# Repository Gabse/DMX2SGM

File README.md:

DMX2SGM
=
DMX512 to Dual SGM256 Converter

=
This simple device converts a standard DMX512 Signal into two SGM256 signals.

It lets you reuse your old SGM gear with almost any standard DMX controller on the market.

The device has 2 independent outputs for DMX channel 1 to 256 and 257 to 512 and can be powered by ether one of them.

Due to its small form factor it can be installed nearly anywhere in the SGM signal path replacing old SGM Regia lighting desks directly. 

9 Dip Swithes let you set a DMX start address, making it easy to expand existing DMX universes.

The opto-isolated input helps you avoiding ground loops between the DMX and the SGM side.

Please also visit my [Blog Post](https://gabsesblog.blogspot.com/2019/12/dmx2sgm.html) for additional information.

Safety information / disclaimer:
=

This device SHOULD NOT be used with anything safety related. It is only meant to control dimmer packs and other lighting fixtures.
It is not allowed to be used with moving stage parts, pyros and similar SFX. Doing so will happen at your OWN RISK!

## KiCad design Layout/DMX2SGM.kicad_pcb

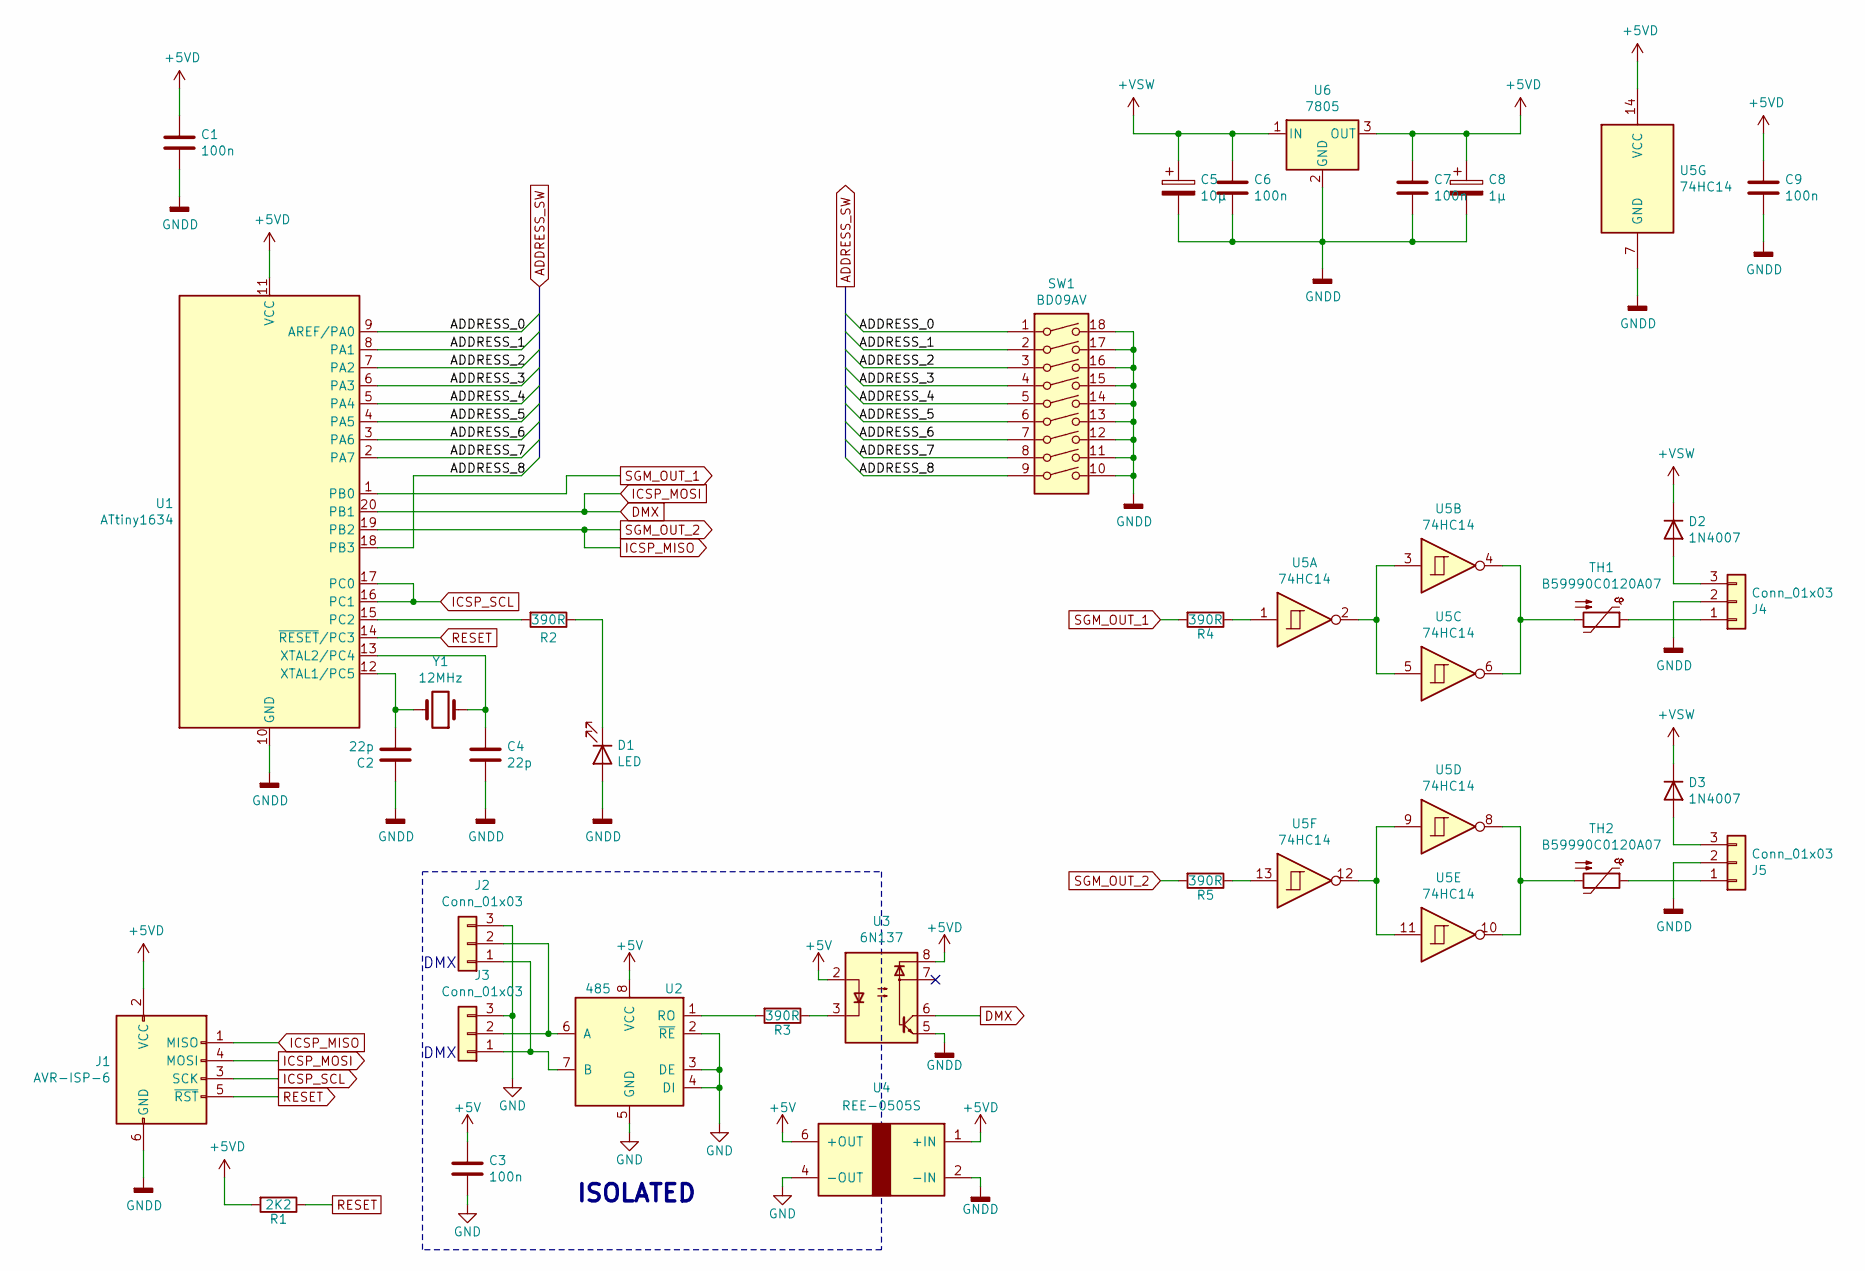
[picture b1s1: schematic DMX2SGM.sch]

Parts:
C1, C3, C6, C9: 100n; C_Disc_D3.0mm_W1.6mm_P2.50mm; MPN C315C103K5R5TA
C2, C4: 22p; C_Disc_D3.0mm_W1.6mm_P2.50mm; MPN C315C229D2G5TA
C5: 10µ; CP_Radial_D6.3mm_P2.50mm; MPN UVZ2A100MED
C7: 100n; C_Disc_D3.0mm_W2.0mm_P2.50mm; MPN C315C103K5R5TA
C8: 1µ; CP_Radial_D6.3mm_P2.50mm; MPN UVZ2C010MED
D1: LED; LED_D5.0mm; MPN TLHY5400-AS12Z
D2, D3: 1N4007; D_DO-15_P12.70mm_Horizontal; MPN 1N4007-E3/54
J1: AVR-ISP-6; PinHeader_2x03_P2.54mm_Vertical; MPN 67996-206HLF
J2, J3, J4, J5: Conn_01x03; PinHeader_1x03_P2.54mm_Vertical; MPN MX-90120-0763
R1: 2K2; R_Axial_DIN0309_L9.0mm_D3.2mm_P12.70mm_Horizontal; MPN MBA02040C2201FCT00
R2, R3, R4, R5: 390R; R_Axial_DIN0309_L9.0mm_D3.2mm_P12.70mm_Horizontal; MPN MBA02040C3900FC100
SW1: BD09AV; MPN BD09AV
TH1, TH2: B59990C0120A07; RV_Disc_D7mm_W3.4mm_P5mm; MPN B59990C0120A070
U1: ATtiny1634; SOIC-20W_7.5x12.8mm_Pitch1.27mm; MPN ATTINY1634-SU
U2: 485; DIP-8_W7.62mm_Socket_LongPads; MPN SN75176BP
U3: 6N137; DIP-8_W7.62mm_Socket_LongPads; MPN 6N137
U4: REE-0505S; RECOM-REE-0505S; MPN REE-0505S
U5: 74HC14; DIP-14_W7.62mm_Socket_LongPads; MPN SN74HC14N
U6: 7805; TO-220-3_Vertical; MPN L7805ABP
Y1: 12MHz; Crystal_HC49-4H_Vertical; MPN LF XTAL003215

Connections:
+5V: C3.1, U2.8 (VCC), U3.2, U4.6 (+OUT)
+5VD: C1.1, C7.1, C8.1, C9.1, J1.2 (VCC), R1.2, U1.11 (VCC), U3.8, U4.1 (+IN), U5.14 (VCC), U6.3 (OUT)
+VSW: C5.1, C6.1, D2.1 (K), D3.1 (K), U6.1 (IN)
/ADDRESS_0: SW1.1, U1.9 (AREF/PA0)
/ADDRESS_1: SW1.2, U1.8 (PA1)
/ADDRESS_2: SW1.3, U1.7 (PA2)
/ADDRESS_3: SW1.4, U1.6 (PA3)
/ADDRESS_4: SW1.5, U1.5 (PA4)
/ADDRESS_5: SW1.6, U1.4 (PA5)
/ADDRESS_6: SW1.7, U1.3 (PA6)
/ADDRESS_7: SW1.8, U1.2 (PA7)
/ADDRESS_8: SW1.9, U1.18 (PB3)
DMX: J1.4 (MOSI), U1.20 (PB1), U3.6
GND: C3.2, J2.3, J3.3, U2.2 (~RE~), U2.3 (DE), U2.4 (DI), U2.5 (GND), U4.4 (-OUT)
GNDD: C1.2, C2.1, C4.2, C5.2, C6.2, C7.2, C8.2, C9.2, D1.2 (A), J1.6 (GND), J4.2, J5.2, SW1.10, SW1.11, SW1.12, SW1.13, SW1.14, SW1.15, SW1.16, SW1.17, SW1.18, U1.10 (GND), U3.5, U4.2 (-IN), U5.7 (GND), U6.2 (GND)
ICSP_MISO: J1.1 (MISO), R5.2, U1.19 (PB2)
ICSP_SCL: J1.3 (SCK), U1.16 (PC1), U1.17 (PC0)
unnamed: C2.2, U1.12 (XTAL1/PC5), Y1.2
unnamed: C4.1, U1.13 (XTAL2/PC4), Y1.1
unnamed: D1.1 (K), R2.1
unnamed: D2.2 (A), J4.3
unnamed: D3.2 (A), J5.3
unnamed: J2.1, J3.1, U2.7 (B)
unnamed: J2.2, J3.2, U2.6 (A)
unnamed: J4.1, TH1.1
unnamed: J5.1, TH2.1
unnamed: R2.2, U1.15 (PC2)
unnamed: R3.1, U3.3
unnamed: R3.2, U2.1 (RO)
unnamed: R4.1, U5.1
unnamed: R5.1, U5.13
unnamed: TH1.2, U5.4, U5.6
unnamed: TH2.2, U5.8, U5.10
unnamed: U5.2, U5.3, U5.5
unnamed: U5.9, U5.11, U5.12
RESET: J1.5 (~RST), R1.1, U1.14 (~RESET~/PC3)
SGM_OUT_1: R4.2, U1.1 (PB0)

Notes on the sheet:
DMX
ISOLATED

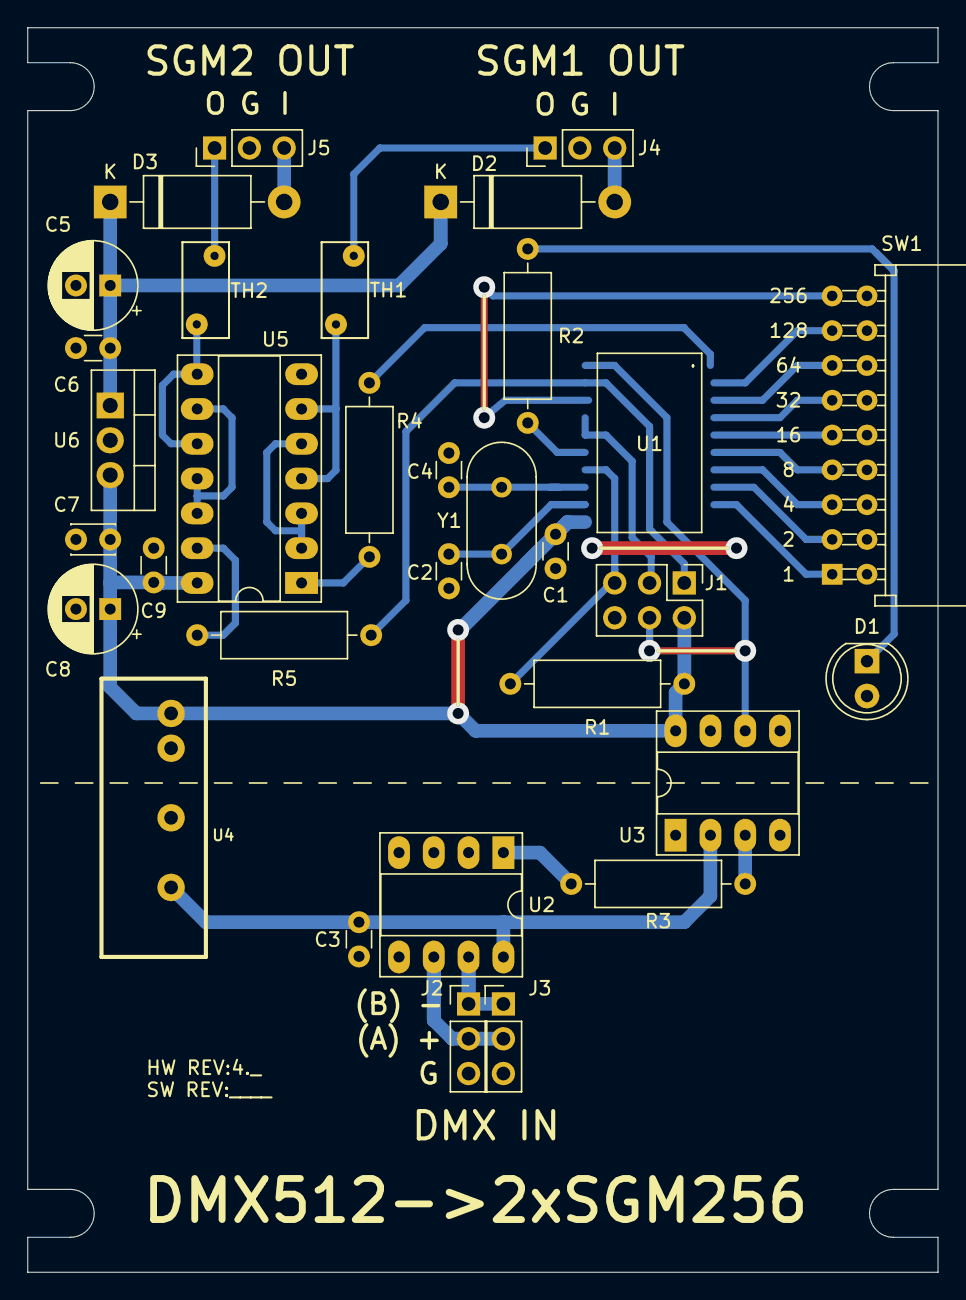
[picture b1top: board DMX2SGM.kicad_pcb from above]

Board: 2 copper layers, 66.4 x 90.9 mm, 32 parts (1 on the bottom side), 37 nets.

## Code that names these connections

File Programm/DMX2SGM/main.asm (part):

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//
//	Attiny Pinout:
//					ADDRESS SW = 0-7= PORTA
//					SGM1	= UART0	= PB0
//					DMX		= UART1 = PB1
//					SGM2	= USI	= PB2
//					ADDRESS SW = 8	= PB3
//					SGM CLOCK	= PC0&PC1
//					LED		=		  PC2
//
//	Fuse Settings: 
//						EXTENDED:	0xF5
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
//******************************General FLAGS*******************************

.equ DSNB			=	0						// DMX Skip Next Byte
.equ DRSB			=	1						// DMX Read Start Byte
.equ LEDT			=	2						// LED Toggle


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	OUT UBRR0H, TEMP							// Set USART 0 baud register MSB to 250kHz
	LDI TEMP, LOW ((F_CPU/(250000*2))-1)		// Set USART 0 baud register LSB to 250kHz
	OUT UBRR0L, TEMP							// Set USART 0 baud register LSB to 250kHz
	SBI DDRC,	 PC0							// Enable clock output
	
	
	
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	LDI YL, 0x00								// Set Y pointer LSB to 0
	LDI YH, 0x02								// Set Y pointer MSB to 2
	CLR SGM2BIT									// Reset SGM2BIT
	LDI TEMP,	1<<USIOIE | 1<<USIWM0 | 1<<USICS1// Set USI to 3Wire mode, clock from PC1 & interrupt on USI overflow
	OUT USICR,	TEMP							// Set USI to 3Wire mode, clock from PC1 & interrupt on USI overflow
	CLR TEMP									// Set USI output to 0
	OUT USIDR, TEMP								// Set USI output to 0
	LDI TEMP, 1<<USIOIF |	10					// Reset USI Overflow Flag & Set USI Counter to 10 to shift SGM interrupts a part 
	OUT USISR, TEMP								// Reset USI Overflow Flag & Set USI Counter to 10 to shift SGM interrupts a part 
	SBI DDRB, PB2								// Set SGM2 pin to Output


//****************************Init USART1 for DMX***************************
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	STS UBRR1H, TEMP							// Set USART 1 baud register MSB to 250kHz
	LDI TEMP,	LOW ((F_CPU/(250000*16))-1)		// Set USART 1 baud register LSB to 250kHz
	STS UBRR1L, TEMP							// Set USART 1 baud register LSB to 250kHz
	SBI PUEB,	PB1								// Enable DMX pullup


//******************************Init Timer for LED**************************
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	STS TCCR1A, TEMP							// Reset Timer/Counter1 Control Register A
	LDI TEMP,	1<<WGM12 | 1<<CS10 | 1<<CS12	// Set Timer/Counter1 Control Register B to Clear Timer on Compare A & Clock/1024
	STS TCCR1B, TEMP							// Set Timer/Counter1 Control Register B to Clear Timer on Compare A & Clock/1024
	SBI DDRC,	PC2								// Set LED pin to output
	SBI PORTC,	PC2								// Turn LED ON


//******************************General Init********************************
	
	LDI TEMP,	1<<WDE							// Enable Watchdog Timer @ 16ms
	OUT WDTCSR,	TEMP							// Enable Watchdog Timer @ 16ms
	CBI DDRB,	PB3								// Set pin PB3 to input
	SBI PUEB,	PB3								// Enable pin PB3 pullup
	LDI TEMP,	0x00							// Set PortA to input 
	OUT DDRA,	TEMP							// Set PortA to input 
	LDI TEMP,	0xFF							// Enable PortA pullup
	OUT PUEA,	TEMP							// Enable PortA pullup
	SER TEMP									// Load TEMP with value for XOR
	IN DMX_ADDRESS_L,	PINB					// Read DMX address bit 8 from DIP switch
	EOR DMX_ADDRESS_L,	TEMP					// Invert register
	BST DMX_ADDRESS_L,	PB3						// Copy DMX address PB3 to T
	BLD DMX_ADDRESS_H,	0						// Copy T to DMX_ADDRESS_H bit 0
	IN DMX_ADDRESS_L,	PINA					// Read DMX address bit 0-7 from DIP switch
	EOR DMX_ADDRESS_L,	TEMP					// Invert register
	LDI SGMOUTREG, 0x88							// Load startbit to SGMOUTREG
	SEI											// Enable global interrupts
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loop:

		// Check if DIP switch address has changed, and force a device reset by not reseting the watchdog if address has changed.
		IN DMX_ADDRESS_L_C,	PINB				// Read DMX address bit 8 from DIP switch
		EOR DMX_ADDRESS_L_C,	TEMP			// Invert register
		BST DMX_ADDRESS_L_C,	PB3				// Copy DMX address PB3 to T
		BLD DMX_ADDRESS_H_C,	0				// Copy T to DMX_ADDRESS_H_C bit 0
		IN DMX_ADDRESS_L_C,	PINA				// Read DMX address bit 0-7 from DIP switch
		EOR DMX_ADDRESS_L_C,	TEMP			// Invert register
		CPSE DMX_ADDRESS_L_C,	DMX_ADDRESS_L	// Compare new address LSB with set address
			RJMP loop								// Jump back to loop if address LSB has changed, forcing a device reset
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	
		// Check if DMX has updated since the last Interrupt, and flash the LED if update has ocoured. Turn the LED ON otherwise.	
		IN S_SREG,	SREG						// Save SREG
		SBI PINC,	PC2							// Toggle LED
		SBRS FLAGS,	LEDT						// Check DMX status for LED toggle
			SBI PORTC,	PC2							// Turn LED ON
		CBR FLAGS,	1<<LEDT						// Clear LEDT flag
		OUT SREG,	S_SREG						// Restore SREG
		RETI									// Exit interrupt
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		LSL SGM2DATA							// Shift SGM2DATA left by 1 possition
		OUT USIDR,	SGMOUTREG					// Output from SGMOUTREG to USART data register
		LDI SGMOUTREG,	1<<USIOIF | 0			// Reset USI Overflow Flag & Set USI Counter to 0
		SBIS PINC,	PC1							// Check clock phase
			LDI SGMOUTREG,	1<<USIOIF | 1			// Correct clock phase (Interrupt on rising edge, output on falling edge)
		OUT USISR,	SGMOUTREG					// Output to USISR
		LDI SGMOUTREG,	0x88					// Load startbit to SGMOUTREG for next Interrupt
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
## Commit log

2021-03-29 Bugfixes & Cleanup
    Code cleanup, Fixing a few bugs, General code optimations
2022-07-24 Fix random reboot, fix OBOE, improve layout
    Fix MCU randomly rebooting.
    Fix DMX address DIP switch off-by-one-error.
    Modify PCB for easier device assembly.

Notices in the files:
Programm/DMX2SGM/main.asm:
Licence: CC BY-NC-SA
Layout/DMX2SGM.kicad_pcb:
CC BY-NC-SA
